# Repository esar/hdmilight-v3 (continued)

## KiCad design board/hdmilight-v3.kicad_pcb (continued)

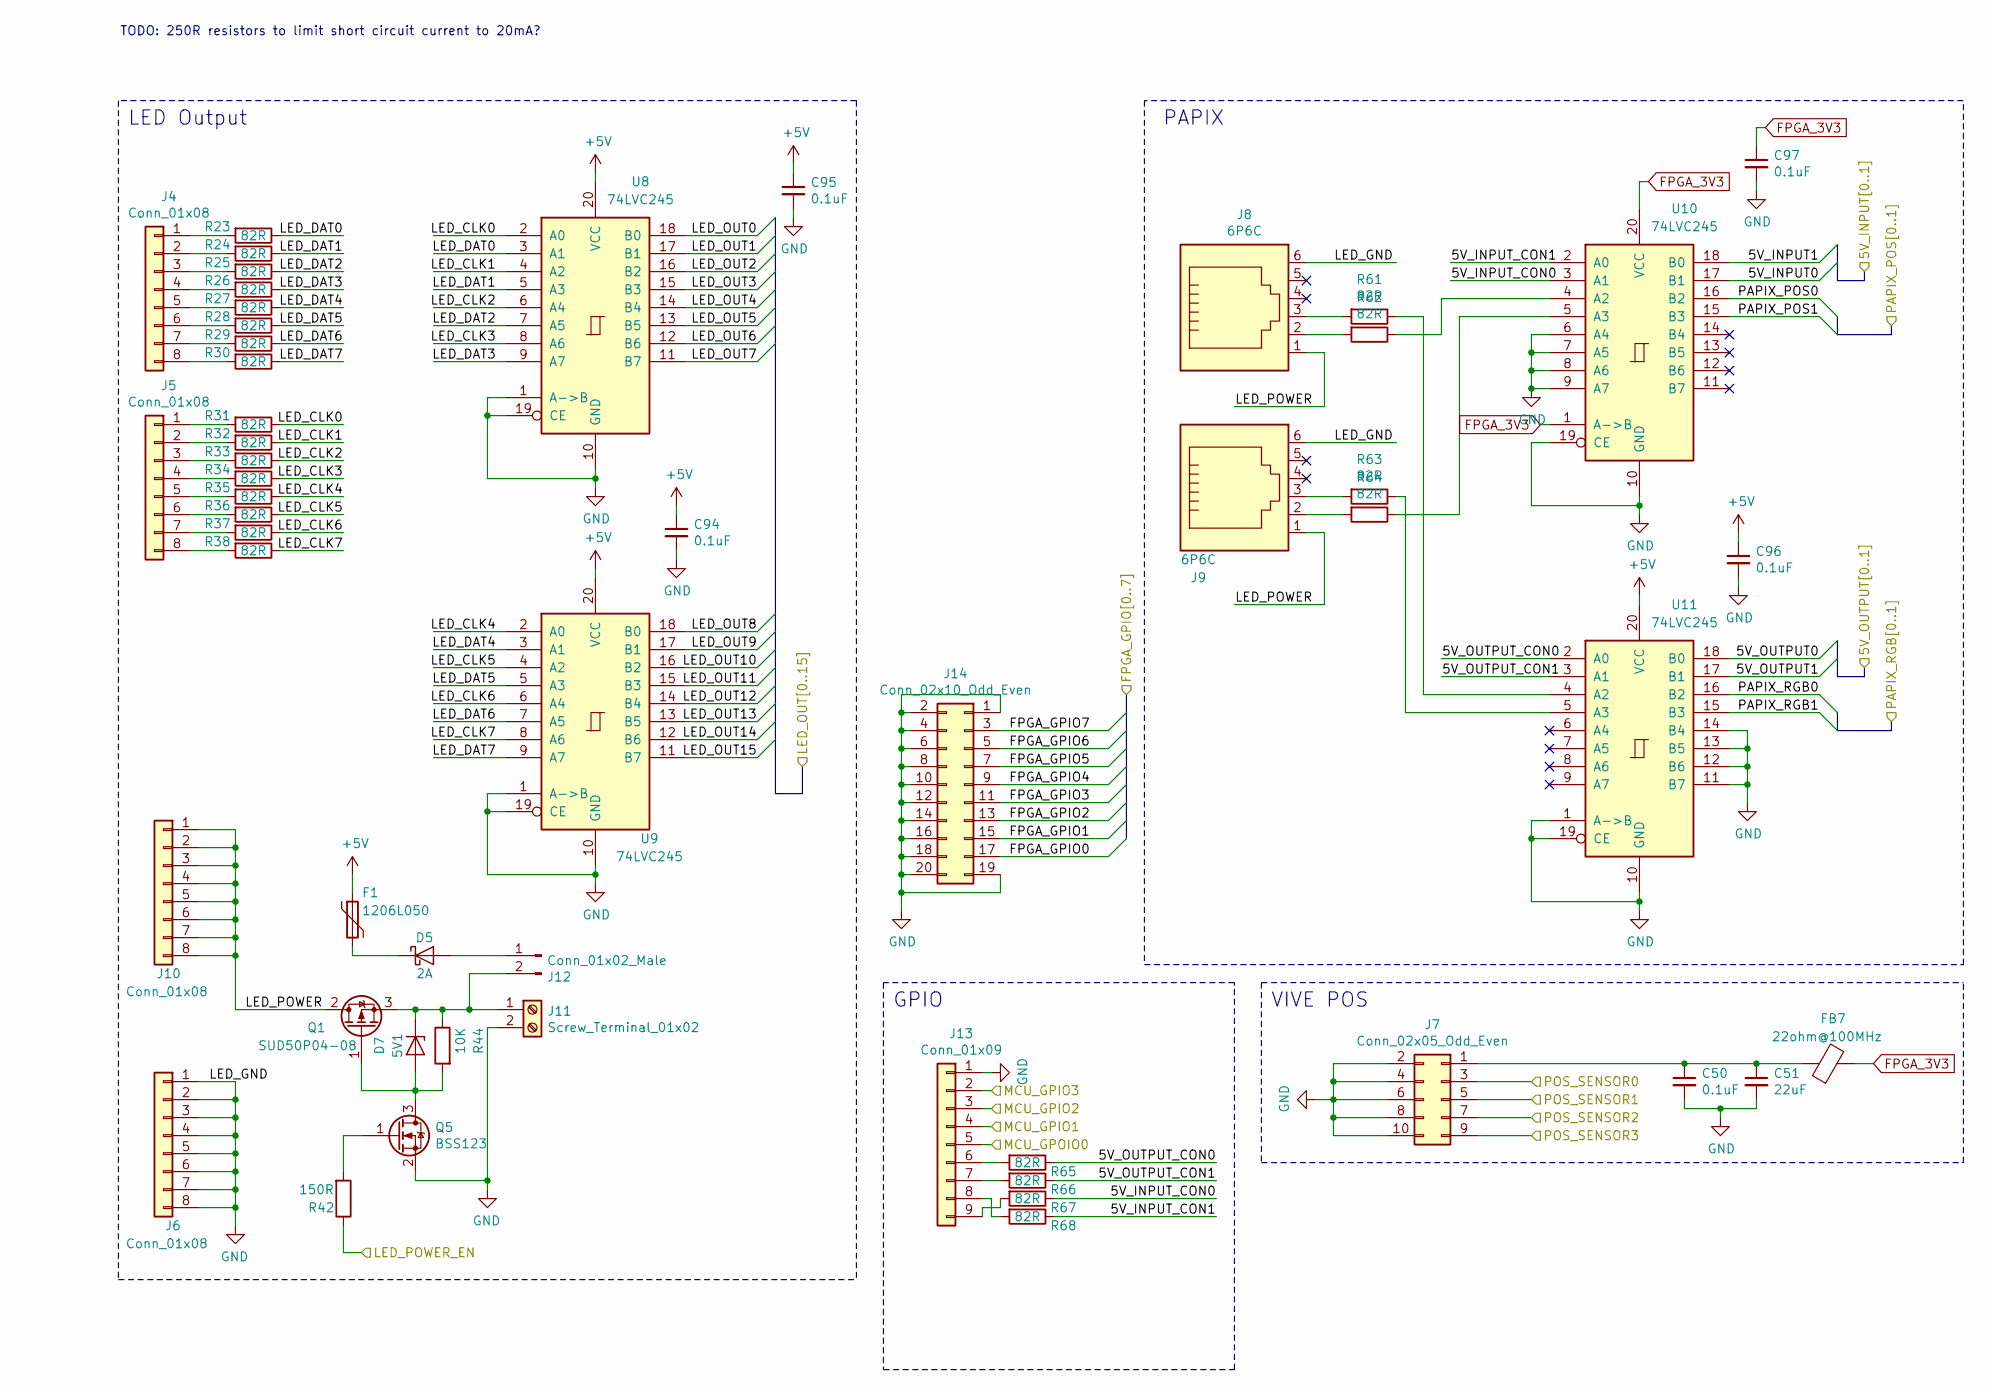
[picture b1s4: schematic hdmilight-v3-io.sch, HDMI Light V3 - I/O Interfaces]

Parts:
C50: 0.1uF; C_0603_1608Metric
C51: 22uF; C_0805_2012Metric
C94, C95, C96, C97: 0.1uF; C_0402_1005Metric
D5: 2A; D_SOD-323
D7: 5V1; D_SOD-323
F1: 1206L050; Fuse_1206_3216Metric
FB7: 22ohm@100MHz; L_0805_2012Metric
J4, J5, J6, J10: Conn_01x08; PinSocket_1x08_P2.54mm_Vertical
J7: Conn_02x05_Odd_Even; IDC-Header_2x05_P2.54mm_Horizontal
J8, J9: 6P6C; RJ12_Amphenol_54601
J11: Screw_Terminal_01x02; TerminalBlock_Phoenix_MKDS-1,5-2_1x02_P5.00mm_Horizontal
J12: Conn_01x02_Male; PinHeader_1x02_P2.54mm_Vertical
J13: Conn_01x09; PinSocket_1x09_P2.54mm_Vertical
J14: Conn_02x10_Odd_Even; PinHeader_2x10_P2.54mm_Horizontal
Q1: SUD50P04-08; TO-252-2
Q5: BSS123; SOT-23
R23, R24, R25, R26, R27, R28, R29, R30, R31, R32, R33, R34, R35, R36, R37, R38, R61, R62, R63, R64, R65, R66, R67, R68: 82R; R_0603_1608Metric
R42: 150R; R_0603_1608Metric
R44: 10K; R_0603_1608Metric
U8, U9, U10, U11: 74LVC245; TSSOP-20_4.4x6.5mm_P0.65mm

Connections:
+5V: C94.1, C95.1, C96.1, F1.1, U8.20 (VCC), U9.20 (VCC), U11.20 (VCC); also elsewhere on the board
/hdmilight-v3-fpga/5V_INPUT0: U10.17 (B1); also elsewhere on the board
/hdmilight-v3-fpga/5V_INPUT1: U10.18 (B0); also elsewhere on the board
/hdmilight-v3-fpga/5V_OUTPUT0: U11.18 (B0); also elsewhere on the board
/hdmilight-v3-fpga/5V_OUTPUT1: U11.17 (B1); also elsewhere on the board
/hdmilight-v3-fpga/FPGA_GPIO0: J14.17; also elsewhere on the board
/hdmilight-v3-fpga/FPGA_GPIO1: J14.15; also elsewhere on the board
/hdmilight-v3-fpga/FPGA_GPIO2: J14.13; also elsewhere on the board
/hdmilight-v3-fpga/FPGA_GPIO3: J14.11; also elsewhere on the board
/hdmilight-v3-fpga/FPGA_GPIO4: J14.9; also elsewhere on the board
/hdmilight-v3-fpga/FPGA_GPIO5: J14.7; also elsewhere on the board
/hdmilight-v3-fpga/FPGA_GPIO6: J14.5; also elsewhere on the board
/hdmilight-v3-fpga/FPGA_GPIO7: J14.3; also elsewhere on the board
/hdmilight-v3-fpga/LED_OUT0: U8.18 (B0); also elsewhere on the board
/hdmilight-v3-fpga/LED_OUT1: U8.17 (B1); also elsewhere on the board
/hdmilight-v3-fpga/LED_OUT2: U8.16 (B2); also elsewhere on the board
/hdmilight-v3-fpga/LED_OUT3: U8.15 (B3); also elsewhere on the board
/hdmilight-v3-fpga/LED_OUT4: U8.14 (B4); also elsewhere on the board
/hdmilight-v3-fpga/LED_OUT5: U8.13 (B5); also elsewhere on the board
/hdmilight-v3-fpga/LED_OUT6: U8.12 (B6); also elsewhere on the board
/hdmilight-v3-fpga/LED_OUT7: U8.11 (B7); also elsewhere on the board
/hdmilight-v3-fpga/LED_OUT8: U9.18 (B0); also elsewhere on the board
/hdmilight-v3-fpga/LED_OUT9: U9.17 (B1); also elsewhere on the board
/hdmilight-v3-fpga/LED_OUT10: U9.16 (B2); also elsewhere on the board
/hdmilight-v3-fpga/LED_OUT11: U9.15 (B3); also elsewhere on the board
/hdmilight-v3-fpga/LED_OUT12: U9.14 (B4); also elsewhere on the board
/hdmilight-v3-fpga/LED_OUT13: U9.13 (B5); also elsewhere on the board
/hdmilight-v3-fpga/LED_OUT14: U9.12 (B6); also elsewhere on the board
/hdmilight-v3-fpga/LED_OUT15: U9.11 (B7); also elsewhere on the board
/hdmilight-v3-fpga/PAPIX_POS0: U10.16 (B2); also elsewhere on the board
/hdmilight-v3-fpga/PAPIX_POS1: U10.15 (B3); also elsewhere on the board
/hdmilight-v3-fpga/PAPIX_RGB0: U11.16 (B2); also elsewhere on the board
/hdmilight-v3-fpga/PAPIX_RGB1: U11.15 (B3); also elsewhere on the board
/hdmilight-v3-fpga/POS_SENSOR0: J7.3; also elsewhere on the board
/hdmilight-v3-fpga/POS_SENSOR1: J7.5; also elsewhere on the board
/hdmilight-v3-fpga/POS_SENSOR2: J7.7; also elsewhere on the board
/hdmilight-v3-fpga/POS_SENSOR3: J7.9; also elsewhere on the board
/hdmilight-v3-io/5V_INPUT_CON0: R67.1, U10.3 (A1)
/hdmilight-v3-io/5V_INPUT_CON1: R68.1, U10.2 (A0)
/hdmilight-v3-io/5V_OUTPUT_CON0: R65.1, U11.2 (A0)
/hdmilight-v3-io/5V_OUTPUT_CON1: R66.1, U11.3 (A1)
/hdmilight-v3-io/LED_CLK0: R31.1, U8.2 (A0)
/hdmilight-v3-io/LED_CLK1: R32.1, U8.4 (A2)
/hdmilight-v3-io/LED_CLK2: R33.1, U8.6 (A4)
/hdmilight-v3-io/LED_CLK3: R34.1, U8.8 (A6)
/hdmilight-v3-io/LED_CLK4: R35.1, U9.2 (A0)
/hdmilight-v3-io/LED_CLK5: R36.1, U9.4 (A2)
/hdmilight-v3-io/LED_CLK6: R37.1, U9.6 (A4)
/hdmilight-v3-io/LED_CLK7: R38.1, U9.8 (A6)
/hdmilight-v3-io/LED_DAT0: R23.1, U8.3 (A1)
/hdmilight-v3-io/LED_DAT1: R24.1, U8.5 (A3)
/hdmilight-v3-io/LED_DAT2: R25.1, U8.7 (A5)
/hdmilight-v3-io/LED_DAT3: R26.1, U8.9 (A7)
/hdmilight-v3-io/LED_DAT4: R27.1, U9.3 (A1)
/hdmilight-v3-io/LED_DAT5: R28.1, U9.5 (A3)
/hdmilight-v3-io/LED_DAT6: R29.1, U9.7 (A5)
/hdmilight-v3-io/LED_DAT7: R30.1, U9.9 (A7)
/hdmilight-v3-io/LED_POWER: J8.1, J9.1, J10.1, J10.2, J10.3, J10.4, J10.5, J10.6, J10.7, J10.8, Q1.2 (D)
/hdmilight-v3-io/LED_POWER_EN: R42.1; also elsewhere on the board
/hdmilight-v3-io/MCU_GPIO1: J13.4; also elsewhere on the board
/hdmilight-v3-io/MCU_GPIO2: J13.3; also elsewhere on the board
/hdmilight-v3-io/MCU_GPIO3: J13.2; also elsewhere on the board
/hdmilight-v3-microcontroller/MCU_GPIO0: J13.5; also elsewhere on the board
FPGA_3V3: C97.1, FB7.2, U10.1 (A->B), U10.20 (VCC); also elsewhere on the board
GND: C50.2, C51.2, C94.2, C95.2, C96.2, C97.2, J6.1, J6.2, J6.3, J6.4, J6.5, J6.6, J6.7, J6.8, J7.2, J7.4, J7.6, J7.8, J7.10, J8.6, J9.6, J11.2, J13.1, J14.1, J14.2, J14.4, J14.6, J14.8, J14.10, J14.12, J14.14, J14.16, J14.18, J14.19, J14.20, Q5.2 (S), U8.1 (A->B), U8.10 (GND), U8.19 (CE), U9.1 (A->B), U9.10 (GND), U9.19 (CE), U10.6 (A4), U10.7 (A5), U10.8 (A6), U10.9 (A7), U10.10 (GND), U10.19 (CE), U11.1 (A->B), U11.10 (GND), U11.11 (B7), U11.12 (B6), U11.13 (B5), U11.14 (B4), U11.19 (CE); also elsewhere on the board
unnamed: C50.1, C51.1, FB7.1, J7.1
unnamed: D5.1 (K), F1.2
unnamed: D5.2 (A), J12.1
unnamed: D7.1 (K), J11.1, J12.2, Q1.3 (S), R44.1
unnamed: D7.2 (A), Q1.1 (G), Q5.3 (D), R44.2
unnamed: J4.1, R23.2
unnamed: J4.2, R24.2
unnamed: J4.3, R25.2
unnamed: J4.4, R26.2
unnamed: J4.5, R27.2
unnamed: J4.6, R28.2
unnamed: J4.7, R29.2
unnamed: J4.8, R30.2
unnamed: J5.1, R31.2
unnamed: J5.2, R32.2
unnamed: J5.3, R33.2
unnamed: J5.4, R34.2
unnamed: J5.5, R35.2
unnamed: J5.6, R36.2
unnamed: J5.7, R37.2
unnamed: J5.8, R38.2
unnamed: J8.2, R62.2
unnamed: J8.3, R61.2
unnamed: J9.2, R64.2
unnamed: J9.3, R63.2
unnamed: J13.6, R65.2
unnamed: J13.7, R66.2
unnamed: J13.8, R68.2
unnamed: J13.9, R67.2
unnamed: Q5.1 (G), R42.2
unnamed: R61.1, U11.4 (A2)
unnamed: R62.1, U10.4 (A2)
unnamed: R63.1, U11.5 (A3)
unnamed: R64.1, U10.5 (A3)

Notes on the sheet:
TODO: 250R resistors to limit short circuit current to 20mA?
LED Output
PAPIX
VIVE POS
GPIO

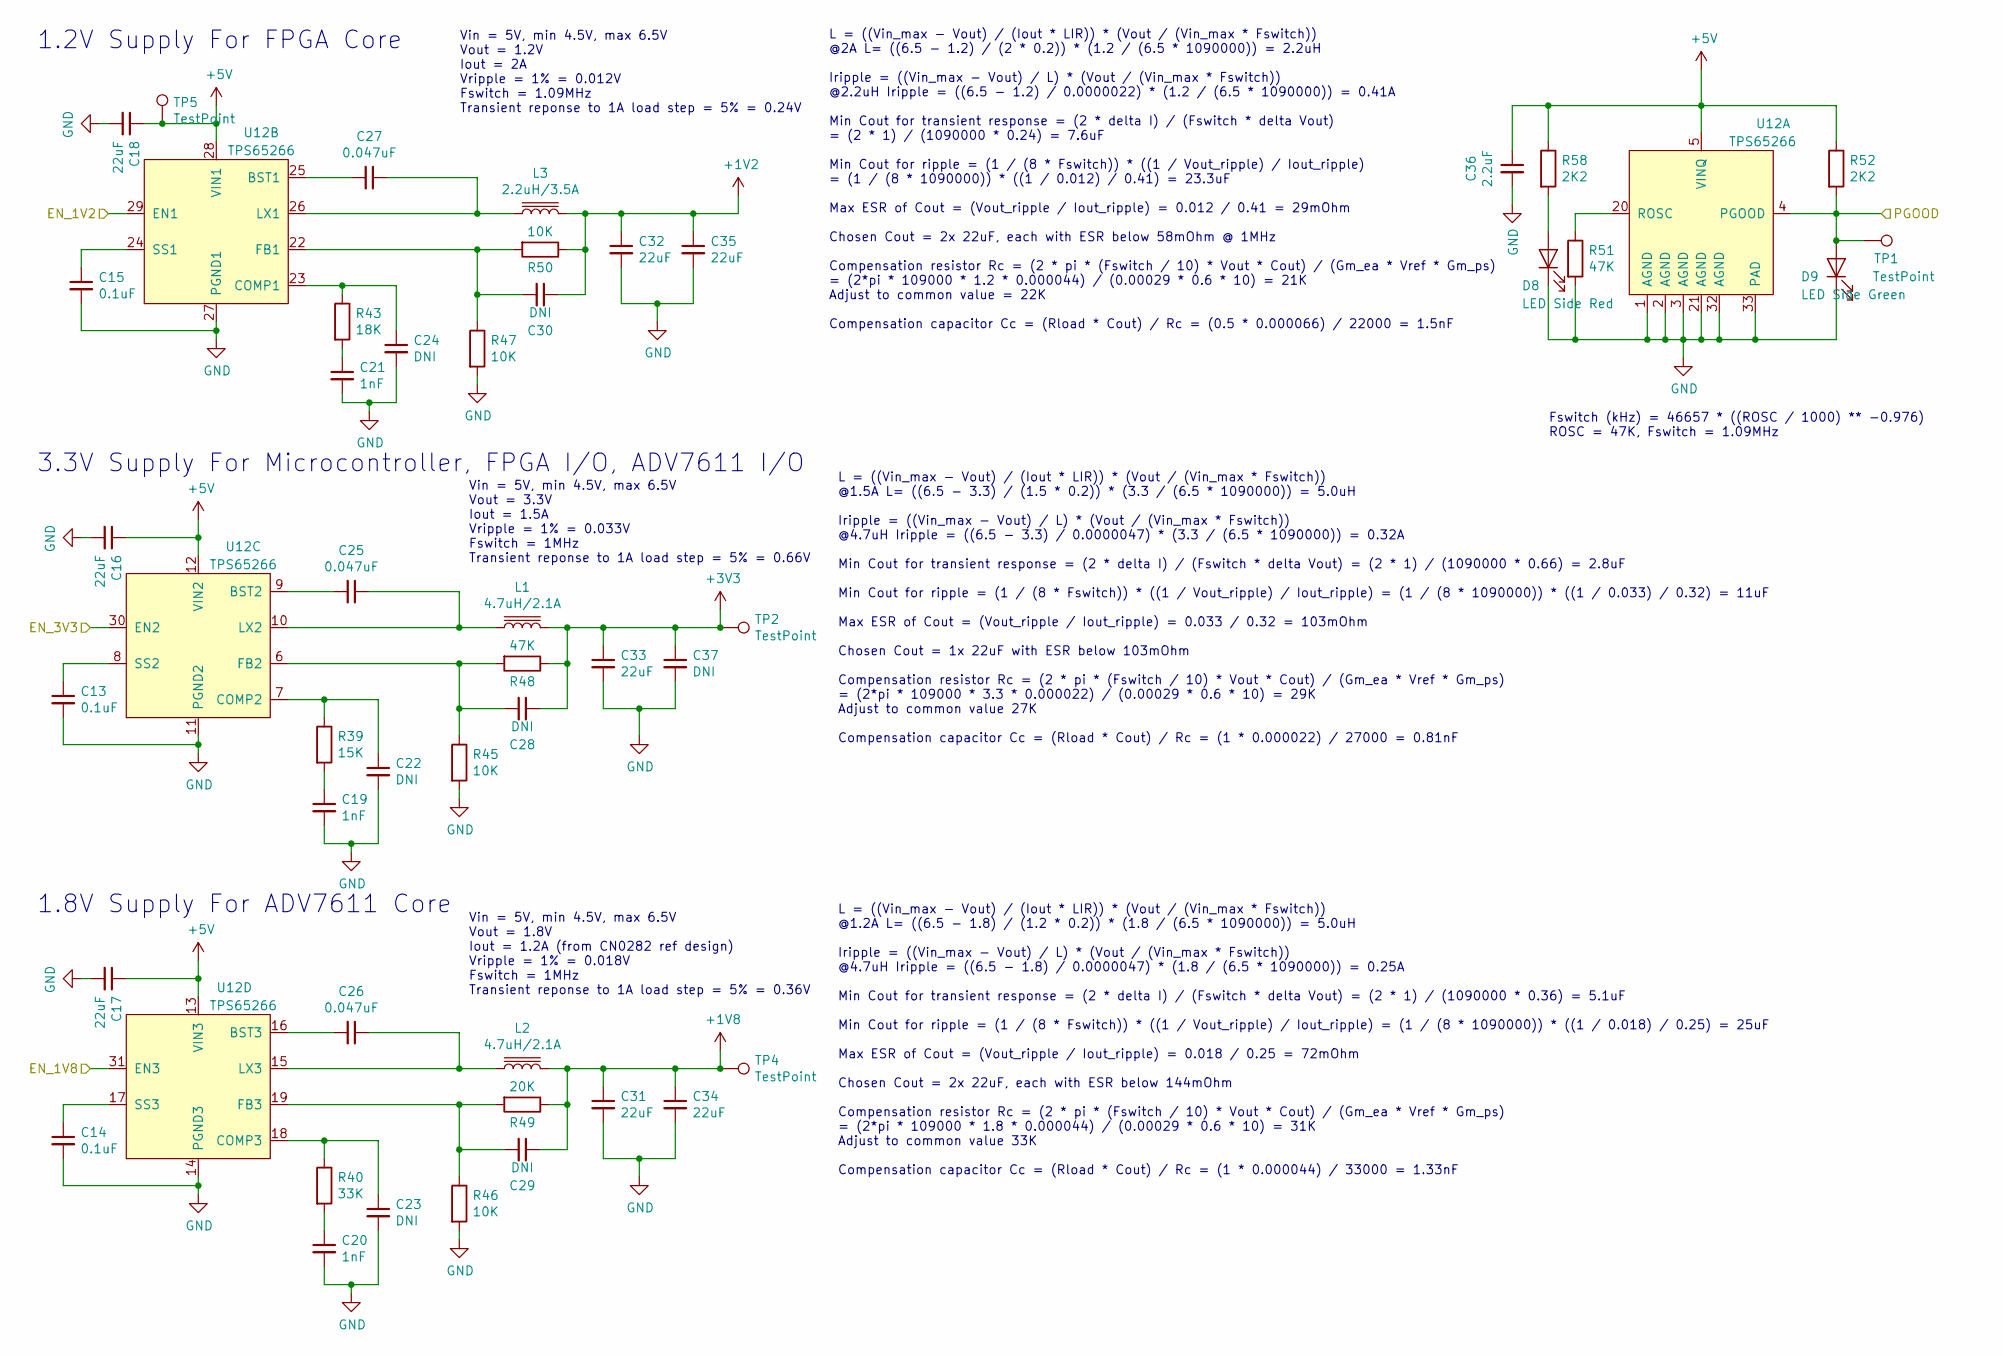
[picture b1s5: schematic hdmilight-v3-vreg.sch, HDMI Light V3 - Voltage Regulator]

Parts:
C13, C14, C15: 0.1uF; C_0603_1608Metric
C16, C17, C18, C31, C32, C33, C34, C35: 22uF; C_0805_2012Metric
C19, C20, C21: 1nF; C_0603_1608Metric
C22, C23, C24, C28, C29, C30: DNI; C_0603_1608Metric
C25, C26, C27: 0.047uF; C_0603_1608Metric
C36: 2.2uF; C_0603_1608Metric
C37: DNI; C_0805_2012Metric
D8: LED Side Red; LED_0603_1608Metric
D9: LED Side Green; LED_0603_1608Metric
L1, L2: 4.7uH/2.1A; L_Bourns-SRN4018
L3: 2.2uH/3.5A; L_Bourns-SRN4018
R39: 15K; R_0603_1608Metric
R40: 33K; R_0603_1608Metric
R43: 18K; R_0603_1608Metric
R45, R46, R47, R50: 10K; R_0603_1608Metric
R48, R51: 47K; R_0603_1608Metric
R49: 20K; R_0603_1608Metric
R52, R58: 2K2; R_0603_1608Metric
TP1, TP2, TP4, TP5: TestPoint; TestPoint_Pad_D1.5mm
U12: TPS65266; QFN-32-1EP_5x5mm_P0.5mm_EP3.1x3.1mm_ThermalVias

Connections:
+1V2: C30.1, C32.1, C35.1, L3.2, R50.1; also elsewhere on the board
+1V8: C29.1, C31.1, C34.1, L2.2, R49.1, TP4.1; also elsewhere on the board
+3V3: C28.1, C33.1, C37.1, L1.2, R48.1, TP2.1; also elsewhere on the board
+5V: C16.1, C17.1, C18.1, C36.1, R52.1, R58.1, TP5.1, U12.5 (VINQ), U12.12 (VIN2), U12.13 (VIN3), U12.28 (VIN1); also elsewhere on the board
/hdmilight-v3-vreg/EN_1V2: U12.29 (EN1); also elsewhere on the board
/hdmilight-v3-vreg/EN_1V8: U12.31 (EN3); also elsewhere on the board
/hdmilight-v3-vreg/EN_3V3: U12.30 (EN2)
/hdmilight-v3-vreg/PGOOD: D9.2 (A), R52.2, TP1.1, U12.4 (PGOOD)
GND: C13.2, C14.2, C15.2, C16.2, C17.2, C18.2, C19.2, C20.2, C21.2, C22.2, C23.2, C24.2, C31.2, C32.2, C33.2, C34.2, C35.2, C36.2, C37.2, D8.1 (K), D9.1 (K), R45.2, R46.2, R47.2, R51.2, U12.1 (AGND), U12.2 (AGND), U12.3 (AGND), U12.11 (PGND2), U12.14 (PGND3), U12.21 (AGND), U12.27 (PGND1), U12.32 (AGND), U12.33 (PAD); also elsewhere on the board
unnamed: C13.1, U12.8 (SS2)
unnamed: C14.1, U12.17 (SS3)
unnamed: C15.1, U12.24 (SS1)
unnamed: C19.1, R39.2
unnamed: C20.1, R40.2
unnamed: C21.1, R43.2
unnamed: C22.1, R39.1, U12.7 (COMP2)
unnamed: C23.1, R40.1, U12.18 (COMP3)
unnamed: C24.1, R43.1, U12.23 (COMP1)
unnamed: C25.1, L1.1, U12.10 (LX2)
unnamed: C25.2, U12.9 (BST2)
unnamed: C26.1, L2.1, U12.15 (LX3)
unnamed: C26.2, U12.16 (BST3)
unnamed: C27.1, L3.1, U12.26 (LX1)
unnamed: C27.2, U12.25 (BST1)
unnamed: C28.2, R45.1, R48.2, U12.6 (FB2)
unnamed: C29.2, R46.1, R49.2, U12.19 (FB3)
unnamed: C30.2, R47.1, R50.2, U12.22 (FB1)
unnamed: D8.2 (A), R58.2
unnamed: R51.1, U12.20 (ROSC)

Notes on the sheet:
1.2V Supply For FPGA Core
Vin = 5V, min 4.5V, max 6.5V Vout = 1.2V Iout = 2A Vripple = 1% = 0.012V Fswitch = 1.09MHz Transient reponse to 1A load step = 5% = 0.24V
L = ((Vin_max - Vout) / (Iout * LIR)) * (Vout / (Vin_max * Fswitch)) @2A L= ((6.5 - 1.2) / (2 * 0.2)) * (1.2 / (6.5 * 1090000)) = 2.2uH Iripple = ((Vin_max - Vout) / L) * (Vout / (Vin_max * Fswitch)) @2.2uH Iripple = ((6.5 - 1.2) / 0.0000022) * (1.2 / (6.5 * 1090000)) = 0.41A Min Cout for transient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
Fswitch (kHz) = 46657 * ((ROSC / 1000) ** -0.976) ROSC = 47K, Fswitch = 1.09MHz
3.3V Supply For Microcontroller, FPGA I/O, ADV7611 I/O
Vin = 5V, min 4.5V, max 6.5V Vout = 3.3V Iout = 1.5A Vripple = 1% = 0.033V Fswitch = 1MHz Transient reponse to 1A load step = 5% = 0.66V
1.8V Supply For ADV7611 Core
Vin = 5V, min 4.5V, max 6.5V Vout = 1.8V Iout = 1.2A (from CN0282 ref design) Vripple = 1% = 0.018V Fswitch = 1MHz Transient reponse to 1A load step = 5% = 0.36V
L = ((Vin_max - Vout) / (Iout * LIR)) * (Vout / (Vin_max * Fswitch)) @1.2A L= ((6.5 - 1.8) / (1.2 * 0.2)) * (1.8 / (6.5 * 1090000)) = 5.0uH Iripple = ((Vin_max - Vout) / L) * (Vout / (Vin_max * Fswitch)) @4.7uH Iripple = ((6.5 - 1.8) / 0.0000047) * (1.8 / (6.5 * 1090000)) = 0.25A Min Cout for trans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
L = ((Vin_max - Vout) / (Iout * LIR)) * (Vout / (Vin_max * Fswitch)) @1.5A L= ((6.5 - 3.3) / (1.5 * 0.2)) * (3.3 / (6.5 * 1090000)) = 5.0uH Iripple = ((Vin_max - Vout) / L) * (Vout / (Vin_max * Fswitch)) @4.7uH Iripple = ((6.5 - 3.3) / 0.0000047) * (3.3 / (6.5 * 1090000)) = 0.32A Min Cout for trans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

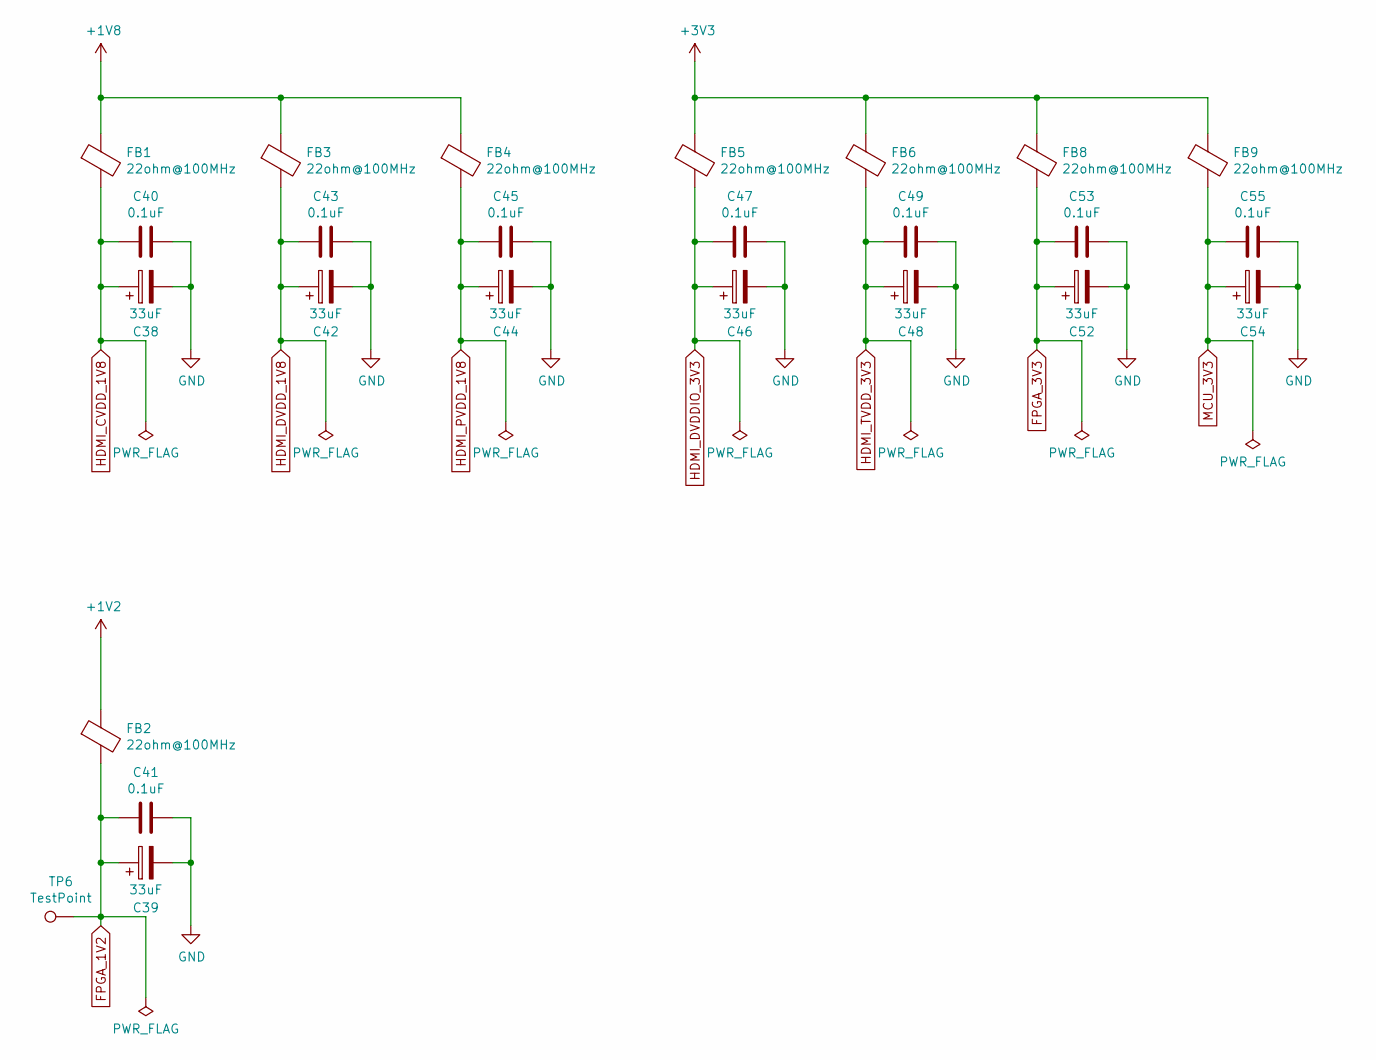
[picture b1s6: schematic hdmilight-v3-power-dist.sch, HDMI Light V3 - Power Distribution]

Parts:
C38, C39, C42, C44, C46, C48, C52, C54: 33uF; CP_EIA-3528-21_Kemet-B
C40, C41, C43, C45, C47, C49, C53, C55: 0.1uF; C_0603_1608Metric
FB1, FB2, FB3, FB4, FB5, FB6, FB8, FB9: 22ohm@100MHz; L_0805_2012Metric
TP6: TestPoint; TestPoint_Pad_D1.5mm

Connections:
+1V2: FB2.1; also elsewhere on the board
+1V8: FB1.1, FB3.1, FB4.1; also elsewhere on the board
+3V3: FB5.1, FB6.1, FB8.1, FB9.1; also elsewhere on the board
FPGA_1V2: C39.1, C41.1, FB2.2, TP6.1; also elsewhere on the board
FPGA_3V3: C52.1, C53.1, FB8.2; also elsewhere on the board
GND: C38.2, C39.2, C40.2, C41.2, C42.2, C43.2, C44.2, C45.2, C46.2, C47.2, C48.2, C49.2, C52.2, C53.2, C54.2, C55.2; also elsewhere on the board
HDMI_CVDD_1V8: C38.1, C40.1, FB1.2; also elsewhere on the board
HDMI_DVDDIO_3V3: C46.1, C47.1, FB5.2; also elsewhere on the board
HDMI_DVDD_1V8: C42.1, C43.1, FB3.2; also elsewhere on the board
HDMI_PVDD_1V8: C44.1, C45.1, FB4.2; also elsewhere on the board
HDMI_TVDD_3V3: C48.1, C49.1, FB6.2; also elsewhere on the board
MCU_3V3: C54.1, C55.1, FB9.2; also elsewhere on the board

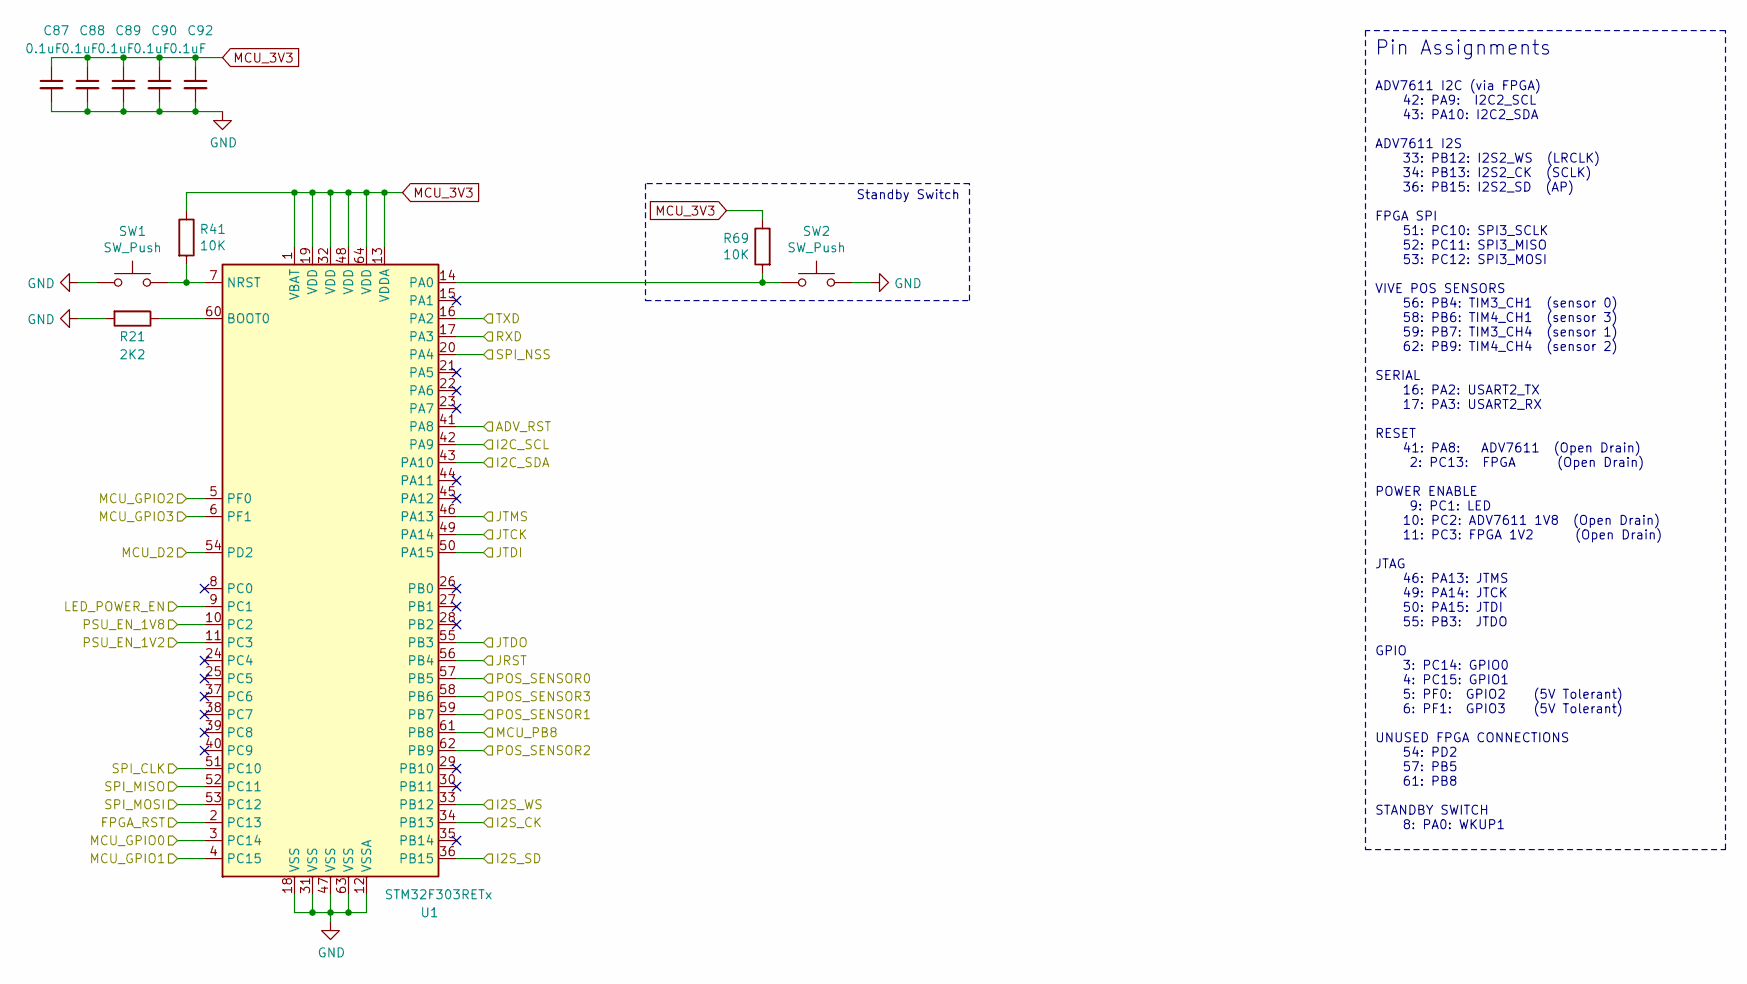
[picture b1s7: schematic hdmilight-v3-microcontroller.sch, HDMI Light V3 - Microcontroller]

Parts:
C87, C88, C89, C90, C92: 0.1uF; C_0402_1005Metric
R21: 2K2; R_0603_1608Metric
R41, R69: 10K; R_0603_1608Metric
SW1: SW_Push; SW_SPST_EVQP0
SW2: SW_Push; SW_Tactile_SPST_Angled_PTS645Vx31-2LFS
U1: STM32F303RETx; LQFP-64_10x10mm_P0.5mm

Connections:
/hdmilight-v3-fpga/ADV_AP: U1.36 (PB15); also elsewhere on the board
/hdmilight-v3-fpga/ADV_LRCLK: U1.33 (PB12); also elsewhere on the board
/hdmilight-v3-fpga/ADV_RST: U1.41 (PA8); also elsewhere on the board
/hdmilight-v3-fpga/ADV_SCL: U1.42 (PA9); also elsewhere on the board
/hdmilight-v3-fpga/ADV_SCLK: U1.34 (PB13); also elsewhere on the board
/hdmilight-v3-fpga/ADV_SDA: U1.43 (PA10); also elsewhere on the board
/hdmilight-v3-fpga/MCU_D2: U1.54 (PD2); also elsewhere on the board
/hdmilight-v3-fpga/MCU_PB8: U1.61 (PB8); also elsewhere on the board
/hdmilight-v3-fpga/POS_SENSOR0: U1.57 (PB5); also elsewhere on the board
/hdmilight-v3-fpga/POS_SENSOR1: U1.59 (PB7); also elsewhere on the board
/hdmilight-v3-fpga/POS_SENSOR2: U1.62 (PB9); also elsewhere on the board
/hdmilight-v3-fpga/POS_SENSOR3: U1.58 (PB6); also elsewhere on the board
/hdmilight-v3-fpga/SPI_CLK: U1.51 (PC10); also elsewhere on the board
/hdmilight-v3-fpga/SPI_MISO: U1.52 (PC11); also elsewhere on the board
/hdmilight-v3-fpga/SPI_MOSI: U1.53 (PC12); also elsewhere on the board
/hdmilight-v3-fpga/SPI_NSS: U1.20 (PA4); also elsewhere on the board
/hdmilight-v3-io/LED_POWER_EN: U1.9 (PC1); also elsewhere on the board
/hdmilight-v3-io/MCU_GPIO1: U1.4 (PC15); also elsewhere on the board
/hdmilight-v3-io/MCU_GPIO2: U1.5 (PF0); also elsewhere on the board
/hdmilight-v3-io/MCU_GPIO3: U1.6 (PF1); also elsewhere on the board
/hdmilight-v3-microcontroller/FPGA_RST: U1.2 (PC13); also elsewhere on the board
/hdmilight-v3-microcontroller/JRST: U1.56 (PB4)
/hdmilight-v3-microcontroller/JTCK: U1.49 (PA14); also elsewhere on the board
/hdmilight-v3-microcontroller/JTDI: U1.50 (PA15); also elsewhere on the board
/hdmilight-v3-microcontroller/JTDO: U1.55 (PB3); also elsewhere on the board
/hdmilight-v3-microcontroller/JTMS: U1.46 (PA13); also elsewhere on the board
/hdmilight-v3-microcontroller/MCU_GPIO0: U1.3 (PC14); also elsewhere on the board
/hdmilight-v3-microcontroller/RXD: U1.17 (PA3); also elsewhere on the board
/hdmilight-v3-microcontroller/TXD: U1.16 (PA2); also elsewhere on the board
/hdmilight-v3-vreg/EN_1V2: U1.11 (PC3); also elsewhere on the board
/hdmilight-v3-vreg/EN_1V8: U1.10 (PC2); also elsewhere on the board
GND: C87.2, C88.2, C89.2, C90.2, C92.2, R21.2, SW1.1, SW2.1, U1.12 (VSSA), U1.18 (VSS), U1.31 (VSS), U1.47 (VSS), U1.63 (VSS); also elsewhere on the board
MCU_3V3: C87.1, C88.1, C89.1, C90.1, C92.1, R41.1, R69.1, U1.1 (VBAT), U1.13 (VDDA), U1.19 (VDD), U1.32 (VDD), U1.48 (VDD), U1.64 (VDD); also elsewhere on the board
unnamed: R21.1, U1.60 (BOOT0)
unnamed: R41.2, SW1.2, U1.7 (NRST)
unnamed: R69.2, SW2.2, U1.14 (PA0)

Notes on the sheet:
ADV7611 I2C (via FPGA) 42: PA9: I2C2_SCL 43: PA10: I2C2_SDA ADV7611 I2S 33: PB12: I2S2_WS (LRCLK) 34: PB13: I2S2_CK (SCLK) 36: PB15: I2S2_SD (AP) FPGA SPI 51: PC10: SPI3_SCLK 52: PC11: SPI3_MISO 53: PC12: SPI3_MOSI VIVE POS SENSORS 56: PB4: TIM3_CH1 (sensor 0) 58: PB6: TIM4_CH1 (sensor 3) 59: PB7: 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
Pin Assignments
Standby Switch

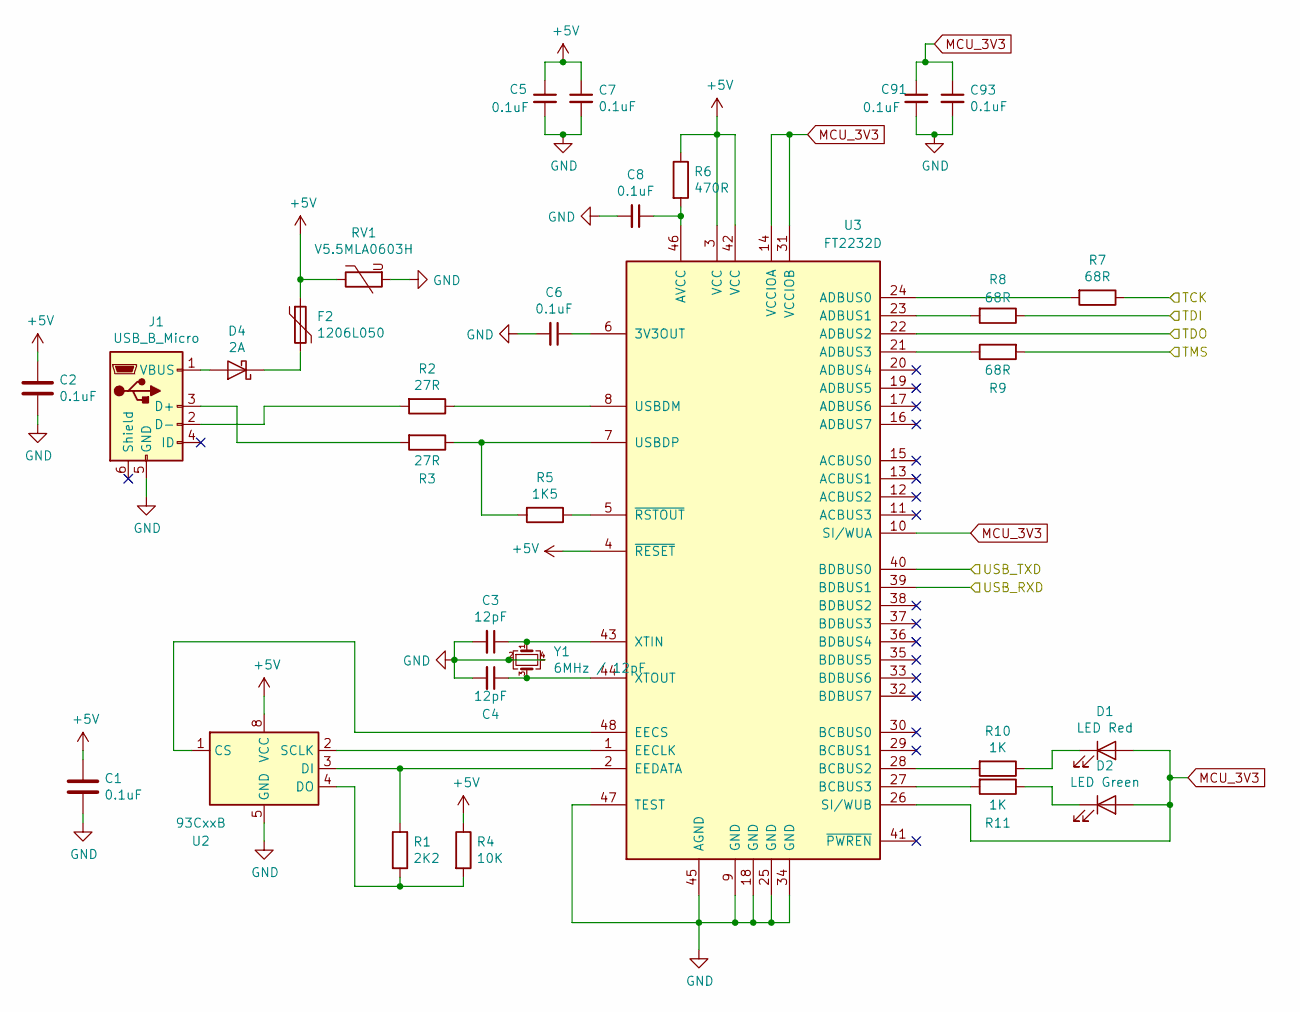
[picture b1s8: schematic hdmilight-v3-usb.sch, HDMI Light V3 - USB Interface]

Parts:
C1, C5, C6, C7, C8, C91, C93: 0.1uF; C_0402_1005Metric
C2: 0.1uF; C_0603_1608Metric
C3, C4: 12pF; C_0603_1608Metric
D1: LED Red; LED_0603_1608Metric
D2: LED Green; LED_0603_1608Metric
D4: 2A; D_SOD-323
F2: 1206L050; Fuse_1206_3216Metric
J1: USB_B_Micro; USB_Micro-B_Amphenol_10103594-0001LF_Horizontal
R1: 2K2; R_0603_1608Metric
R2, R3: 27R; R_0603_1608Metric
R4: 10K; R_0603_1608Metric
R5: 1K5; R_0603_1608Metric
R6: 470R; R_0603_1608Metric
R7, R8, R9: 68R; R_0603_1608Metric
R10, R11: 1K; R_0603_1608Metric
RV1: V5.5MLA0603H; R_0603_1608Metric
U2: 93CxxB; SOIC-8_3.9x4.9mm_P1.27mm
U3: FT2232D; LQFP-48_7x7mm_P0.5mm
Y1: 6MHz / 12pF; Crystal_SMD_7050-4Pin_7.0x5.0mm

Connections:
+5V: C1.1, C2.1, C5.1, C7.1, F2.1, R4.1, R6.1, RV1.1, U2.8 (VCC), U3.3 (VCC), U3.4 (~RESET), U3.42 (VCC); also elsewhere on the board
/hdmilight-v3-fpga/TDI: R8.1; also elsewhere on the board
/hdmilight-v3-microcontroller/JTCK: R7.1; also elsewhere on the board
/hdmilight-v3-microcontroller/JTDO: U3.22 (ADBUS2); also elsewhere on the board
/hdmilight-v3-microcontroller/JTMS: R9.2; also elsewhere on the board
/hdmilight-v3-microcontroller/RXD: U3.40 (BDBUS0); also elsewhere on the board
/hdmilight-v3-microcontroller/TXD: U3.39 (BDBUS1); also elsewhere on the board
GND: C1.2, C2.2, C3.2, C4.2, C5.2, C6.2, C7.2, C8.2, C91.2, C93.2, J1.5 (GND), RV1.2, U2.5 (GND), U3.9 (GND), U3.18 (GND), U3.25 (GND), U3.34 (GND), U3.45 (AGND), U3.47 (TEST), Y1.2, Y1.4; also elsewhere on the board
MCU_3V3: C91.1, C93.1, D1.2 (A), D2.2 (A), U3.10 (SI/WUA), U3.14 (VCCIOA), U3.26 (SI/WUB), U3.31 (VCCIOB); also elsewhere on the board
unnamed: C3.1, U3.43 (XTIN), Y1.1
unnamed: C4.1, U3.44 (XTOUT), Y1.3
unnamed: C6.1, U3.6 (3V3OUT)
unnamed: C8.1, R6.2, U3.46 (AVCC)
unnamed: D1.1 (K), R10.1
unnamed: D2.1 (K), R11.1
unnamed: D4.1 (K), F2.2
unnamed: D4.2 (A), J1.1 (VBUS)
unnamed: J1.2 (D-), R2.2
unnamed: J1.3 (D+), R3.2
unnamed: R1.1, U2.3 (DI), U3.2 (EEDATA)
unnamed: R1.2, R4.2, U2.4 (DO)
unnamed: R2.1, U3.8 (USBDM)
unnamed: R3.1, R5.2, U3.7 (USBDP)
unnamed: R5.1, U3.5 (~RSTOUT)
unnamed: R7.2, U3.24 (ADBUS0)
unnamed: R8.2, U3.23 (ADBUS1)
unnamed: R9.1, U3.21 (ADBUS3)
unnamed: R10.2, U3.28 (BCBUS2)
unnamed: R11.2, U3.27 (BCBUS3)
unnamed: U2.1 (CS), U3.48 (EECS)
unnamed: U2.2 (SCLK), U3.1 (EECLK)
